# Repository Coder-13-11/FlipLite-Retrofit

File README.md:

# FlipLite Retrofit

A small attachment that flips a bathroom fan switch and turns it off on a timer. The plug-in tube light will use an Amazon smart plug through Alexa.

Start with one fan attachment and one smart plug. The fan arm should park clear so the switch still works by hand. The adjustable fan timer starts at 12 minutes and runs locally. Check that the tube light comes back on when power returns before relying on its smart plug.

## Files

| Folder or file | Contents |
|---|---|
| [CAD](design/cad) | Editable Python parameters, STEP solids and STL print candidates |
| [Electronics](design/electronics) | Editable EAGLE schematic, unrouted board and component list |
| [KiCad board](design/A1/electronics/node.kicad_pcb) | Imported placement draft |
| [Control code](design/firmware) | Python behavior reference and tests |
| [Firmware draft](design/A1/firmware) | Incomplete ESP32 scaffolding |
| [Current plan](design/design-basis.md) | Fan servo plus tube smart plug |
| [Build list](design/active-build-list.md) | Current quantities and print scope |
| [BOM](bom.csv) | Parts categories and links; incomplete pricing |
| [Build guide](design/assembly-and-test.md) | Fit checks and bench tests still needed |
| [Status](STATUS.md) | What exists and what is missing |

## Status

The design is unfinished. The PCB needs routing, verified footprints and electrical checks. The battery is not selected. Firmware and a complete assembly with electronics still need work. No physical prototype has been built or tested.

Inline cradle/finger/optical files are from an earlier approach and are not part of the current build. See [retired files](design/cad/RETIRED.md). Images are CAD or placement renders, not photographs or screenshots of a finished device.

## Checks

Earlier A0 reports recorded 21 passing checks. The upload rerun passed 20; one geometry test could not import OCP.OCP. These tests cover selected geometry/interfaces and control rules, not physical or electrical performance.

```sh
python -m pip install cadquery==2.8.0 trimesh matplotlib pytest
python -m pytest design/validation/test_artifacts.py design/firmware/test_control.py -q
```

## Assistance

AI helped create the CAD, circuit drafts, code and documentation. The files need the builder's own review and revisions. This repository does not establish eligibility for a funding program.

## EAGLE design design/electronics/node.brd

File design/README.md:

# Design files

Start with the [repository README](../README.md) and [current plan](design-basis.md).

The current build uses a servo for the bathroom fan and a smart plug for the tube light. Older inline actuator parts are retained as history and should not be printed for this build.

[Status and missing requirements](../STATUS.md) lists what still needs to be finished. [View notes](previews/README.md) explains the simplified renders.

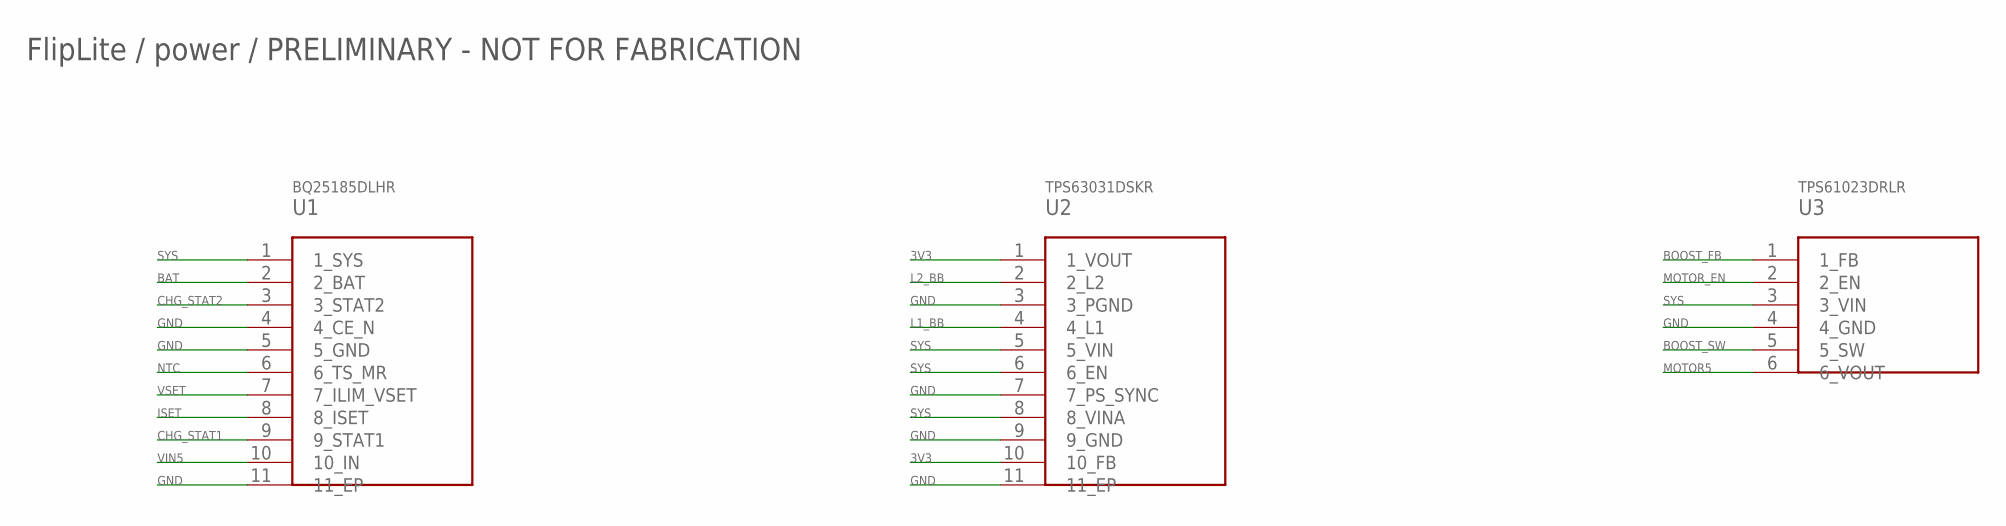
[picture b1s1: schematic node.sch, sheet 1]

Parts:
U1: BQ25185DLHR; U1_PKG
U2: TPS63031DSKR; U2_PKG
U3: TPS61023DRLR; U3_PKG

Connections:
3V3: U2.1 (1_VOUT), U2.10 (10_FB); also elsewhere on the board
BAT: U1.2 (2_BAT); also elsewhere on the board
BOOST_FB: U3.1 (1_FB); also elsewhere on the board
BOOST_SW: U3.5 (5_SW); also elsewhere on the board
CHG_STAT1: U1.9 (9_STAT1); also elsewhere on the board
CHG_STAT2: U1.3 (3_STAT2); also elsewhere on the board
GND: U1.4 (4_CE_N), U1.5 (5_GND), U1.11 (11_EP), U2.3 (3_PGND), U2.7 (7_PS_SYNC), U2.9 (9_GND), U2.11 (11_EP), U3.4 (4_GND); also elsewhere on the board
ISET: U1.8 (8_ISET); also elsewhere on the board
L1_BB: U2.4 (4_L1); also elsewhere on the board
L2_BB: U2.2 (2_L2); also elsewhere on the board
MOTOR5: U3.6 (6_VOUT); also elsewhere on the board
MOTOR_EN: U3.2 (2_EN); also elsewhere on the board
NTC: U1.6 (6_TS_MR); also elsewhere on the board
SYS: U1.1 (1_SYS), U2.5 (5_VIN), U2.6 (6_EN), U2.8 (8_VINA), U3.3 (3_VIN); also elsewhere on the board
VIN5: U1.10 (10_IN); also elsewhere on the board
VSET: U1.7 (7_ILIM_VSET); also elsewhere on the board

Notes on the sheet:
FlipLite / power / PRELIMINARY - NOT FOR FABRICATION

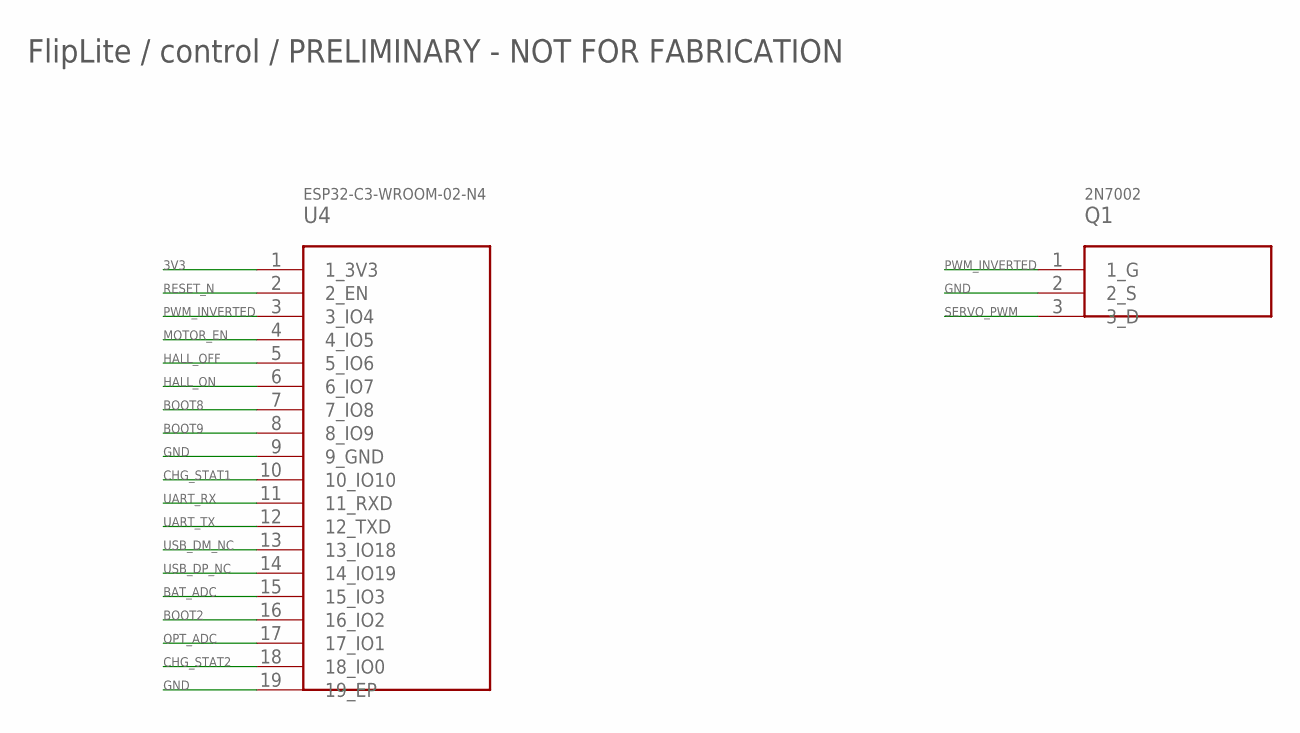
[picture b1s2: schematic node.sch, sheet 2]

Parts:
Q1: 2N7002; Q1_PKG
U4: ESP32-C3-WROOM-02-N4; U4_PKG

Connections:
3V3: U4.1 (1_3V3); also elsewhere on the board
BAT_ADC: U4.15 (15_IO3); also elsewhere on the board
BOOT2: U4.16 (16_IO2); also elsewhere on the board
BOOT8: U4.7 (7_IO8); also elsewhere on the board
BOOT9: U4.8 (8_IO9); also elsewhere on the board
CHG_STAT1: U4.10 (10_IO10); also elsewhere on the board
CHG_STAT2: U4.18 (18_IO0); also elsewhere on the board
GND: Q1.2 (2_S), U4.9 (9_GND), U4.19 (19_EP); also elsewhere on the board
HALL_OFF: U4.5 (5_IO6); also elsewhere on the board
HALL_ON: U4.6 (6_IO7); also elsewhere on the board
MOTOR_EN: U4.4 (4_IO5); also elsewhere on the board
OPT_ADC: U4.17 (17_IO1); also elsewhere on the board
PWM_INVERTED: Q1.1 (1_G), U4.3 (3_IO4); also elsewhere on the board
RESET_N: U4.2 (2_EN); also elsewhere on the board
SERVO_PWM: Q1.3 (3_D); also elsewhere on the board
UART_RX: U4.11 (11_RXD); also elsewhere on the board
UART_TX: U4.12 (12_TXD); also elsewhere on the board
USB_DM_NC: U4.13 (13_IO18)
USB_DP_NC: U4.14 (14_IO19)

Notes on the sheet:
FlipLite / control / PRELIMINARY - NOT FOR FABRICATION

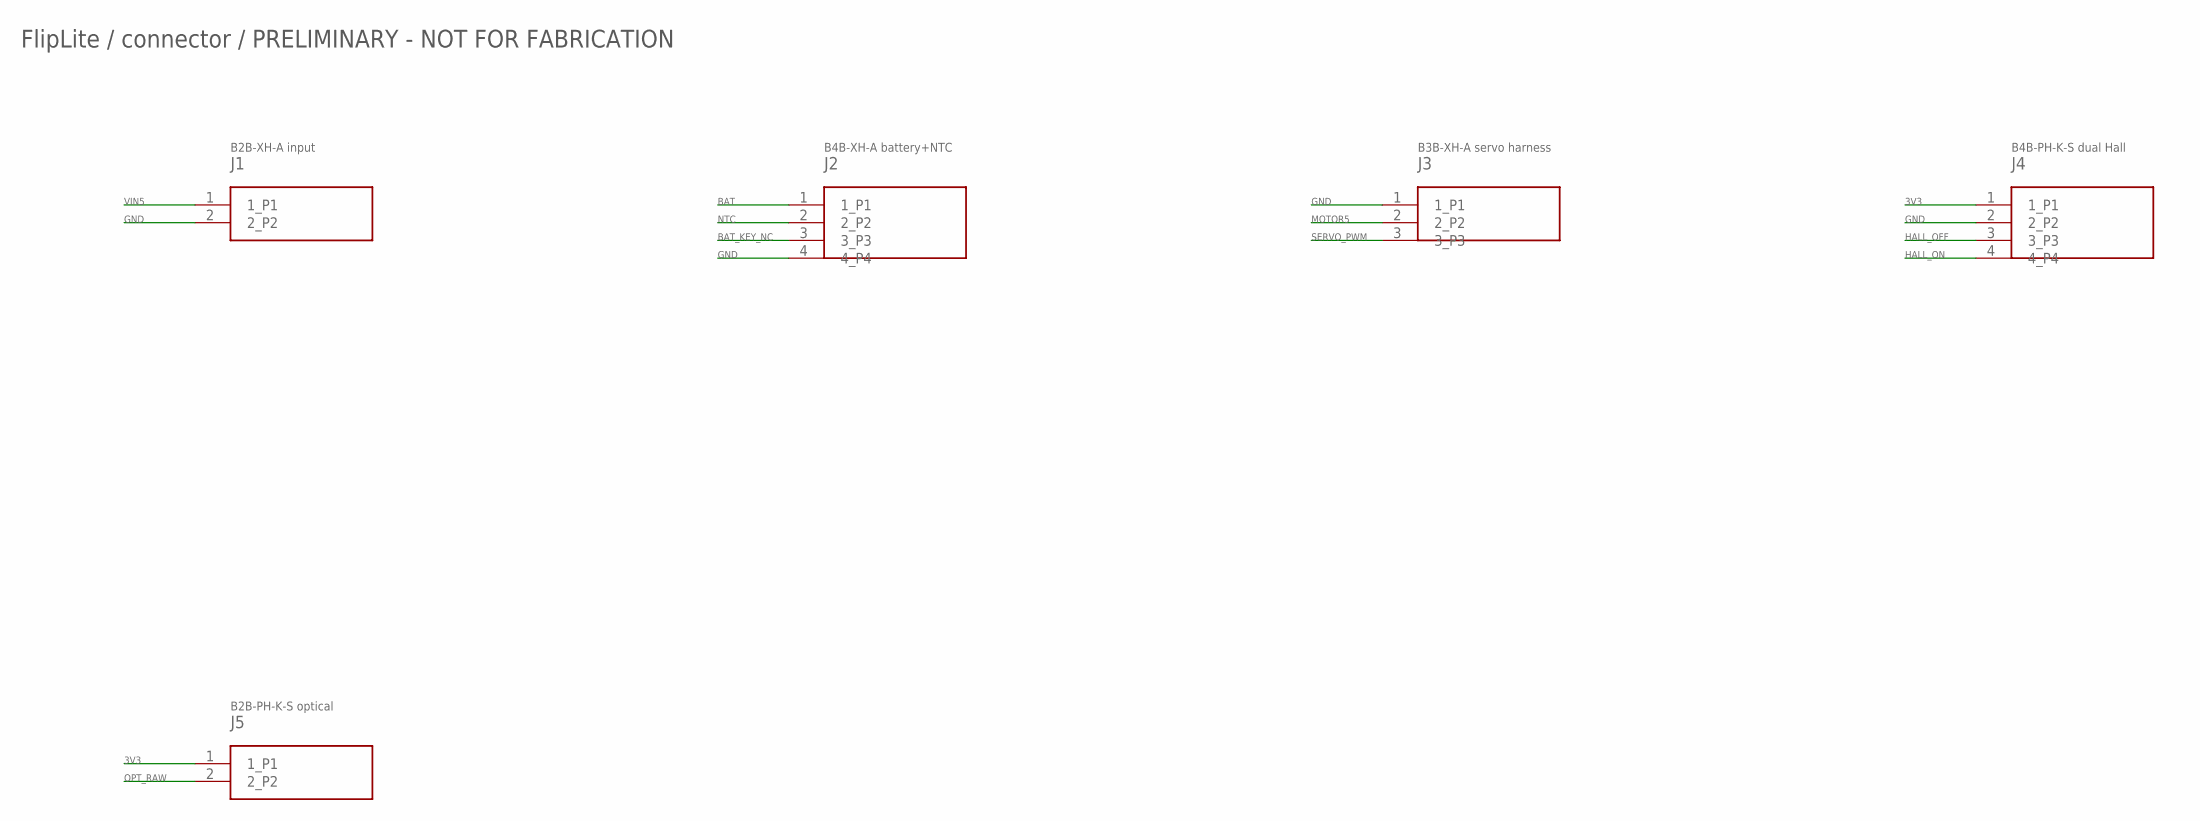
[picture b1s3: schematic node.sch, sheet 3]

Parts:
J1: B2B-XH-A input; J1_PKG
J2: B4B-XH-A battery+NTC; J2_PKG
J3: B3B-XH-A servo harness; J3_PKG
J4: B4B-PH-K-S dual Hall; J4_PKG
J5: B2B-PH-K-S optical; J5_PKG

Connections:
3V3: J4.1 (1_P1), J5.1 (1_P1); also elsewhere on the board
BAT: J2.1 (1_P1); also elsewhere on the board
BAT_KEY_NC: J2.3 (3_P3)
GND: J1.2 (2_P2), J2.4 (4_P4), J3.1 (1_P1), J4.2 (2_P2); also elsewhere on the board
HALL_OFF: J4.3 (3_P3); also elsewhere on the board
HALL_ON: J4.4 (4_P4); also elsewhere on the board
MOTOR5: J3.2 (2_P2); also elsewhere on the board
NTC: J2.2 (2_P2); also elsewhere on the board
OPT_RAW: J5.2 (2_P2); also elsewhere on the board
SERVO_PWM: J3.3 (3_P3); also elsewhere on the board
VIN5: J1.1 (1_P1); also elsewhere on the board

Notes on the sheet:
FlipLite / connector / PRELIMINARY - NOT FOR FABRICATION

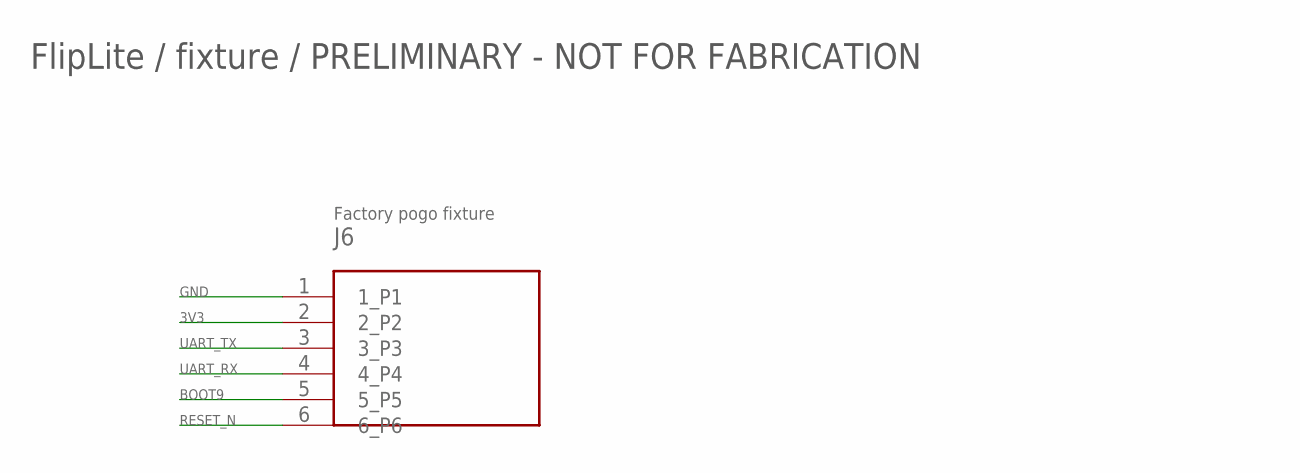
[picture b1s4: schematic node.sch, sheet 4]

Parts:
J6: Factory pogo fixture; J6_PKG

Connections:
3V3: J6.2 (2_P2); also elsewhere on the board
BOOT9: J6.5 (5_P5); also elsewhere on the board
GND: J6.1 (1_P1); also elsewhere on the board
RESET_N: J6.6 (6_P6); also elsewhere on the board
UART_RX: J6.4 (4_P4); also elsewhere on the board
UART_TX: J6.3 (3_P3); also elsewhere on the board

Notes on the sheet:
FlipLite / fixture / PRELIMINARY - NOT FOR FABRICATION

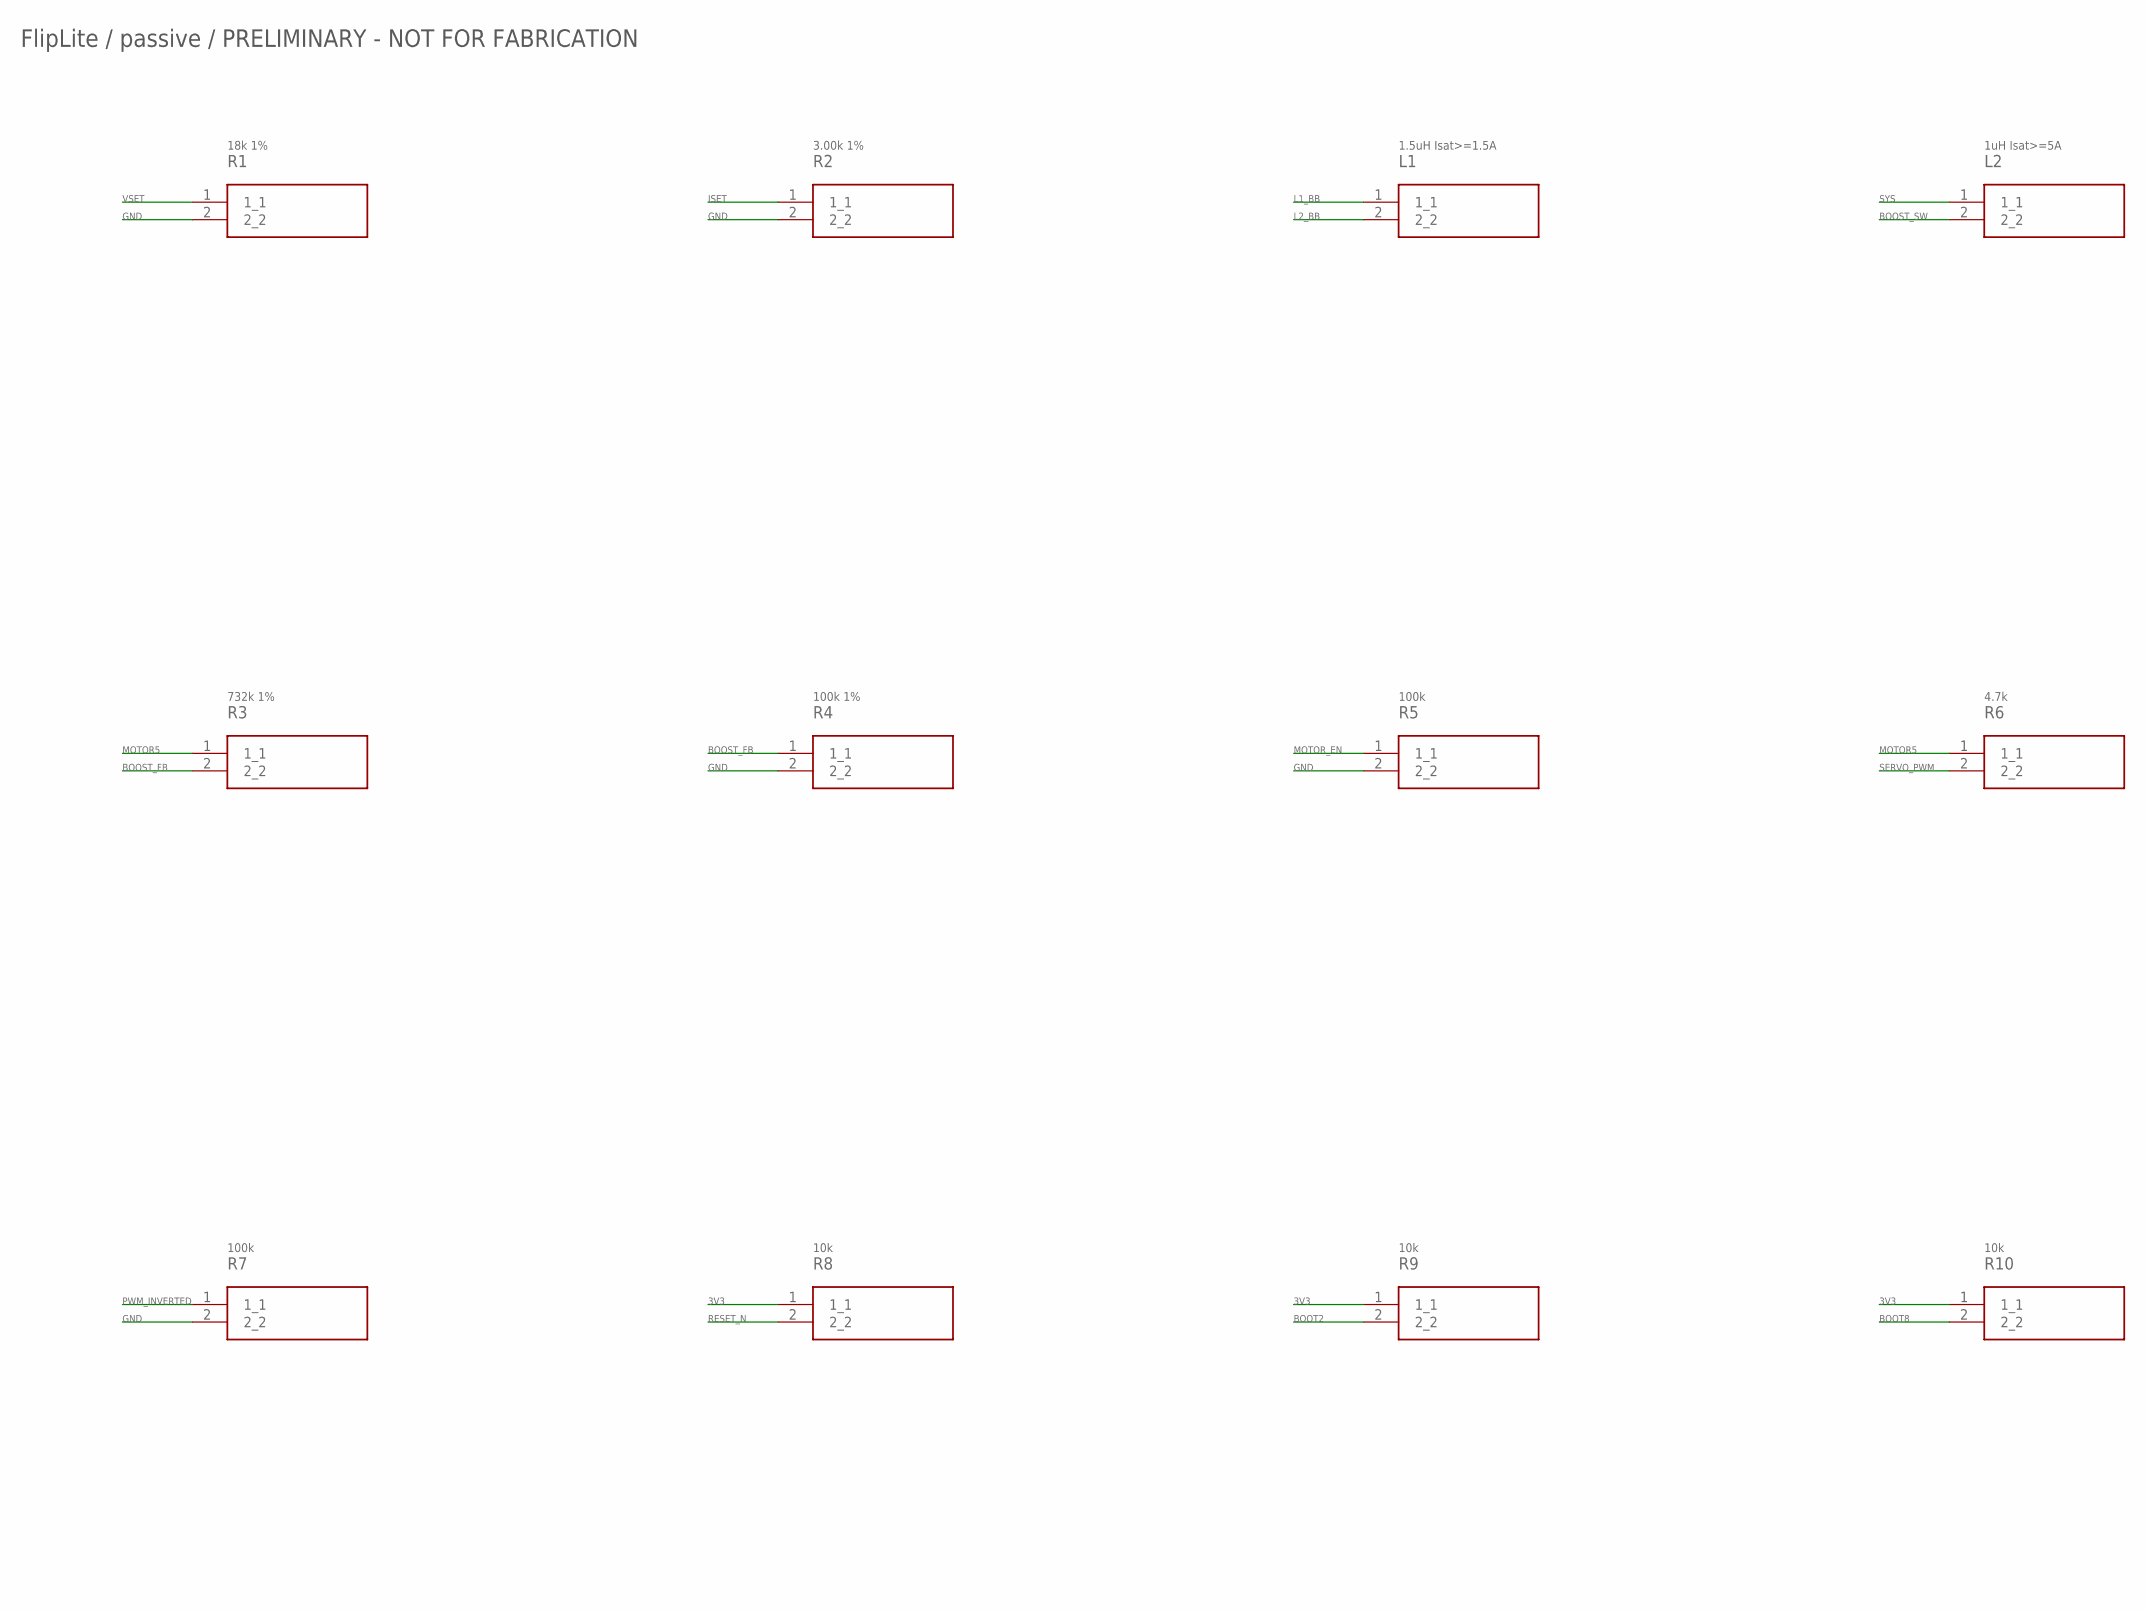
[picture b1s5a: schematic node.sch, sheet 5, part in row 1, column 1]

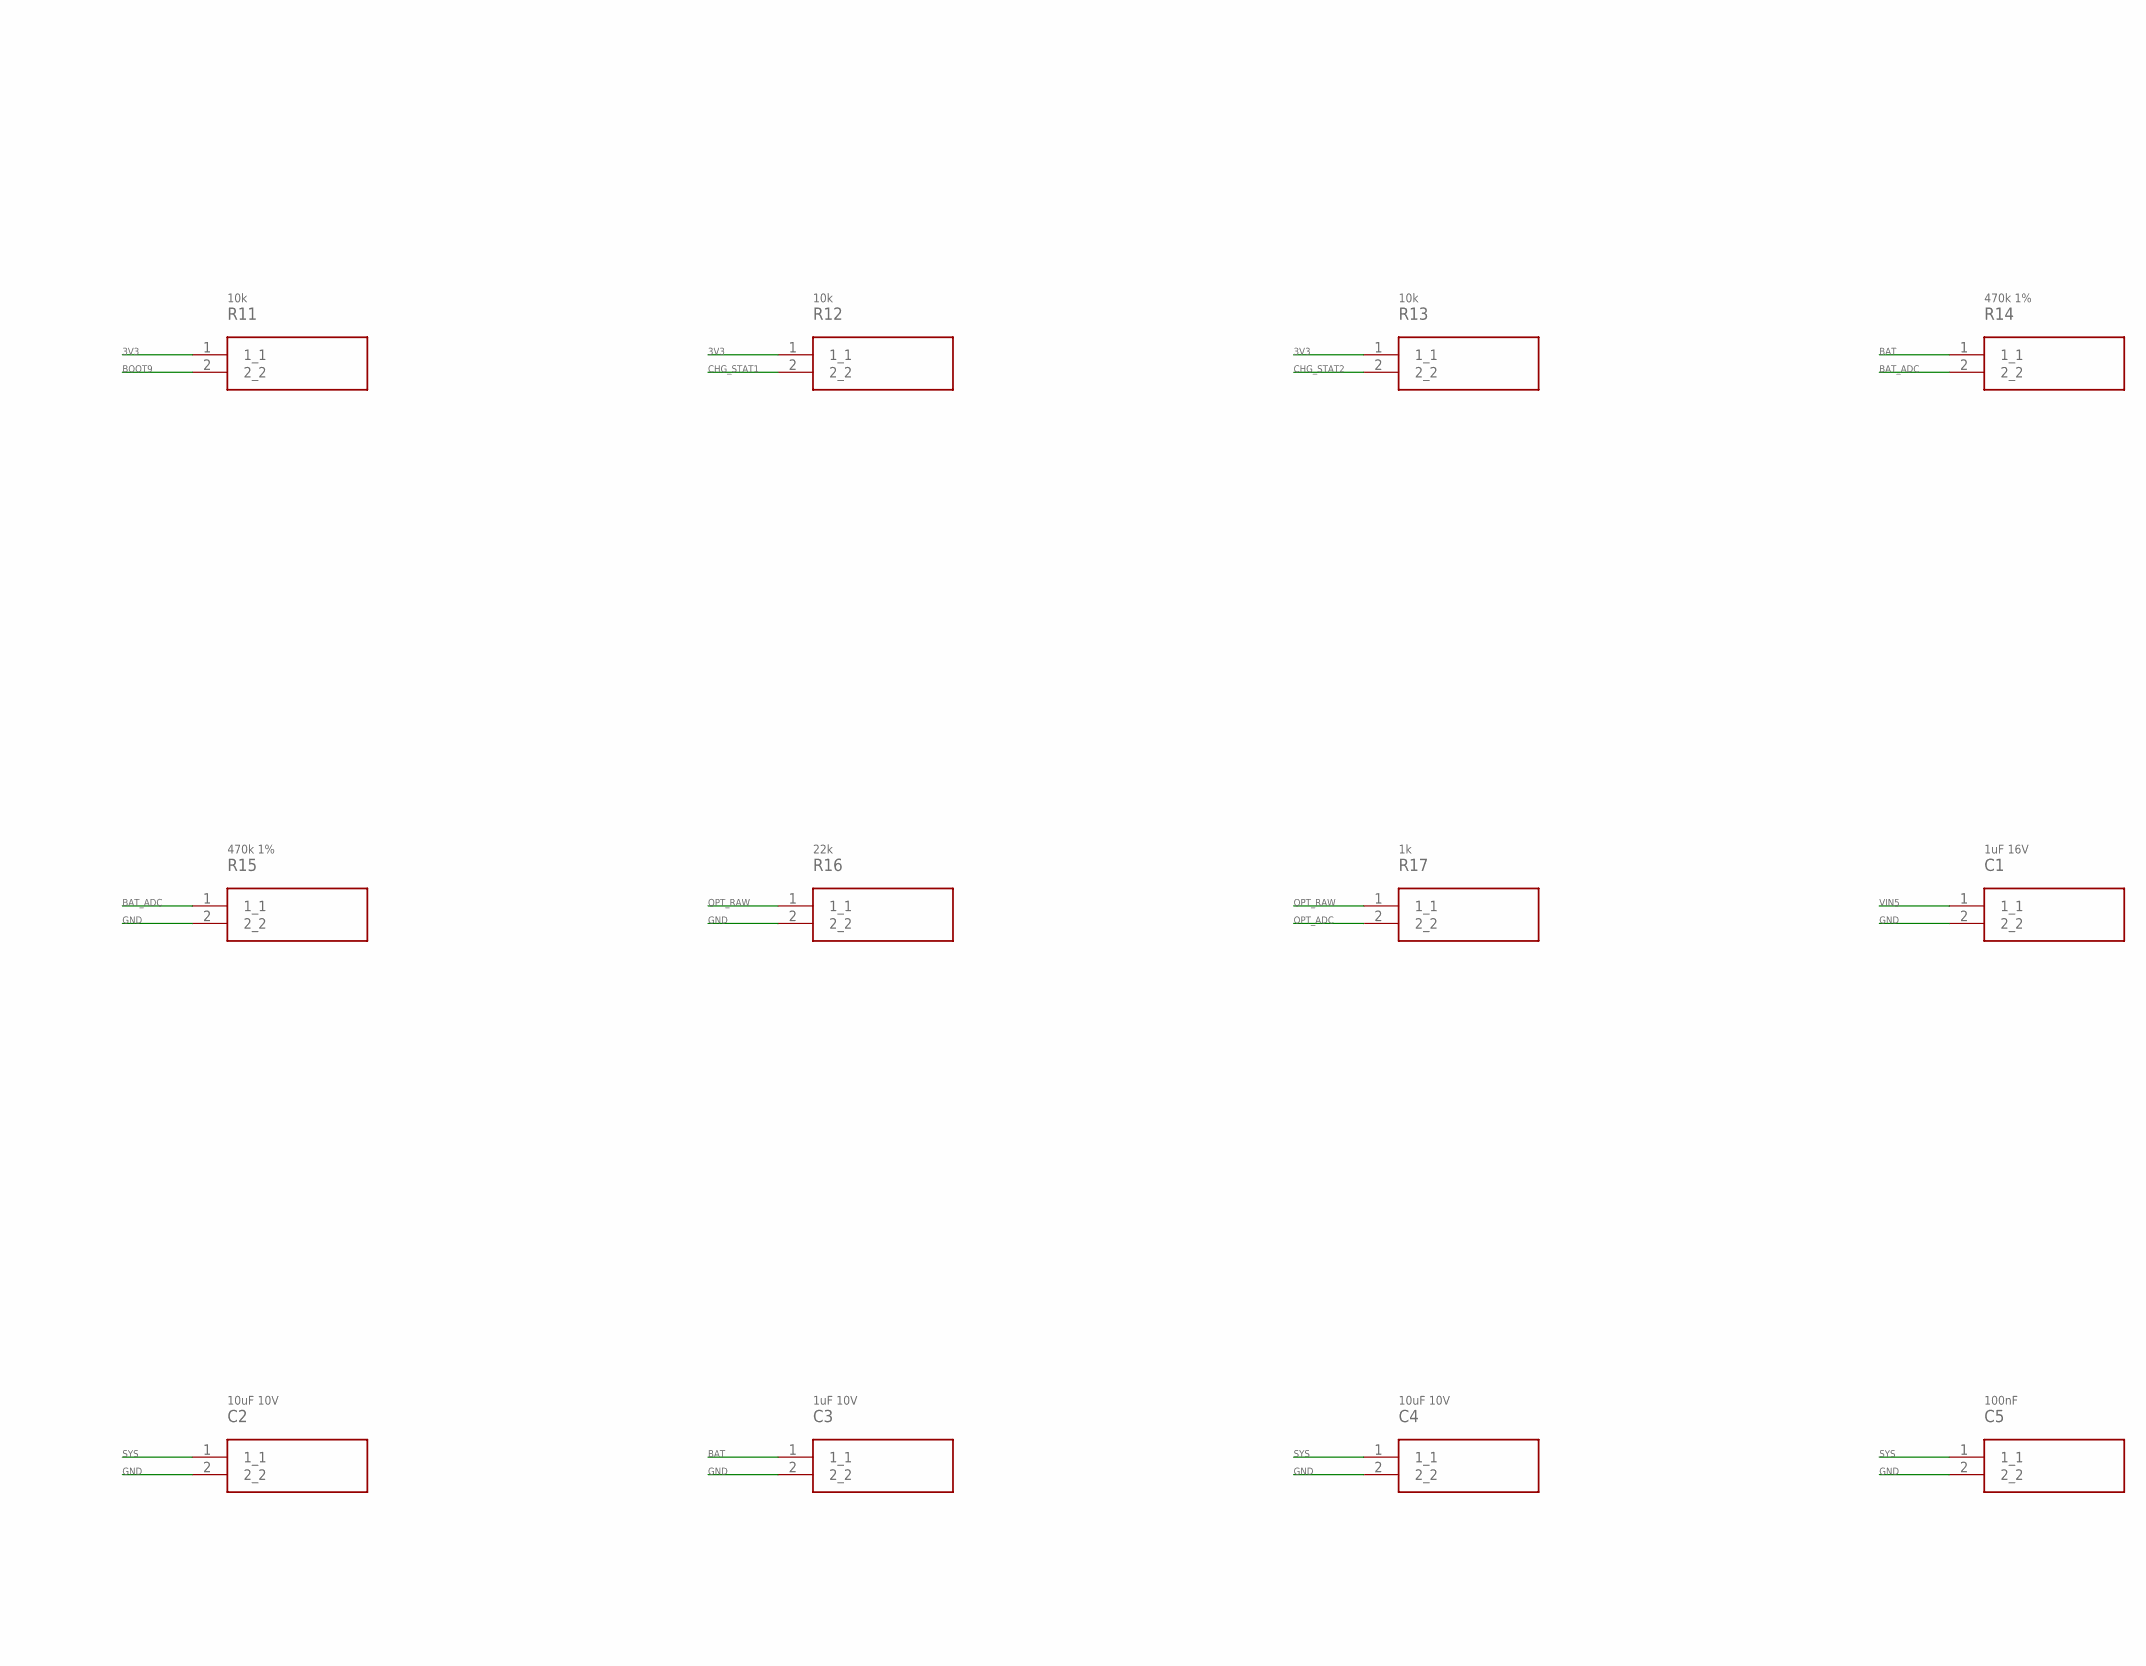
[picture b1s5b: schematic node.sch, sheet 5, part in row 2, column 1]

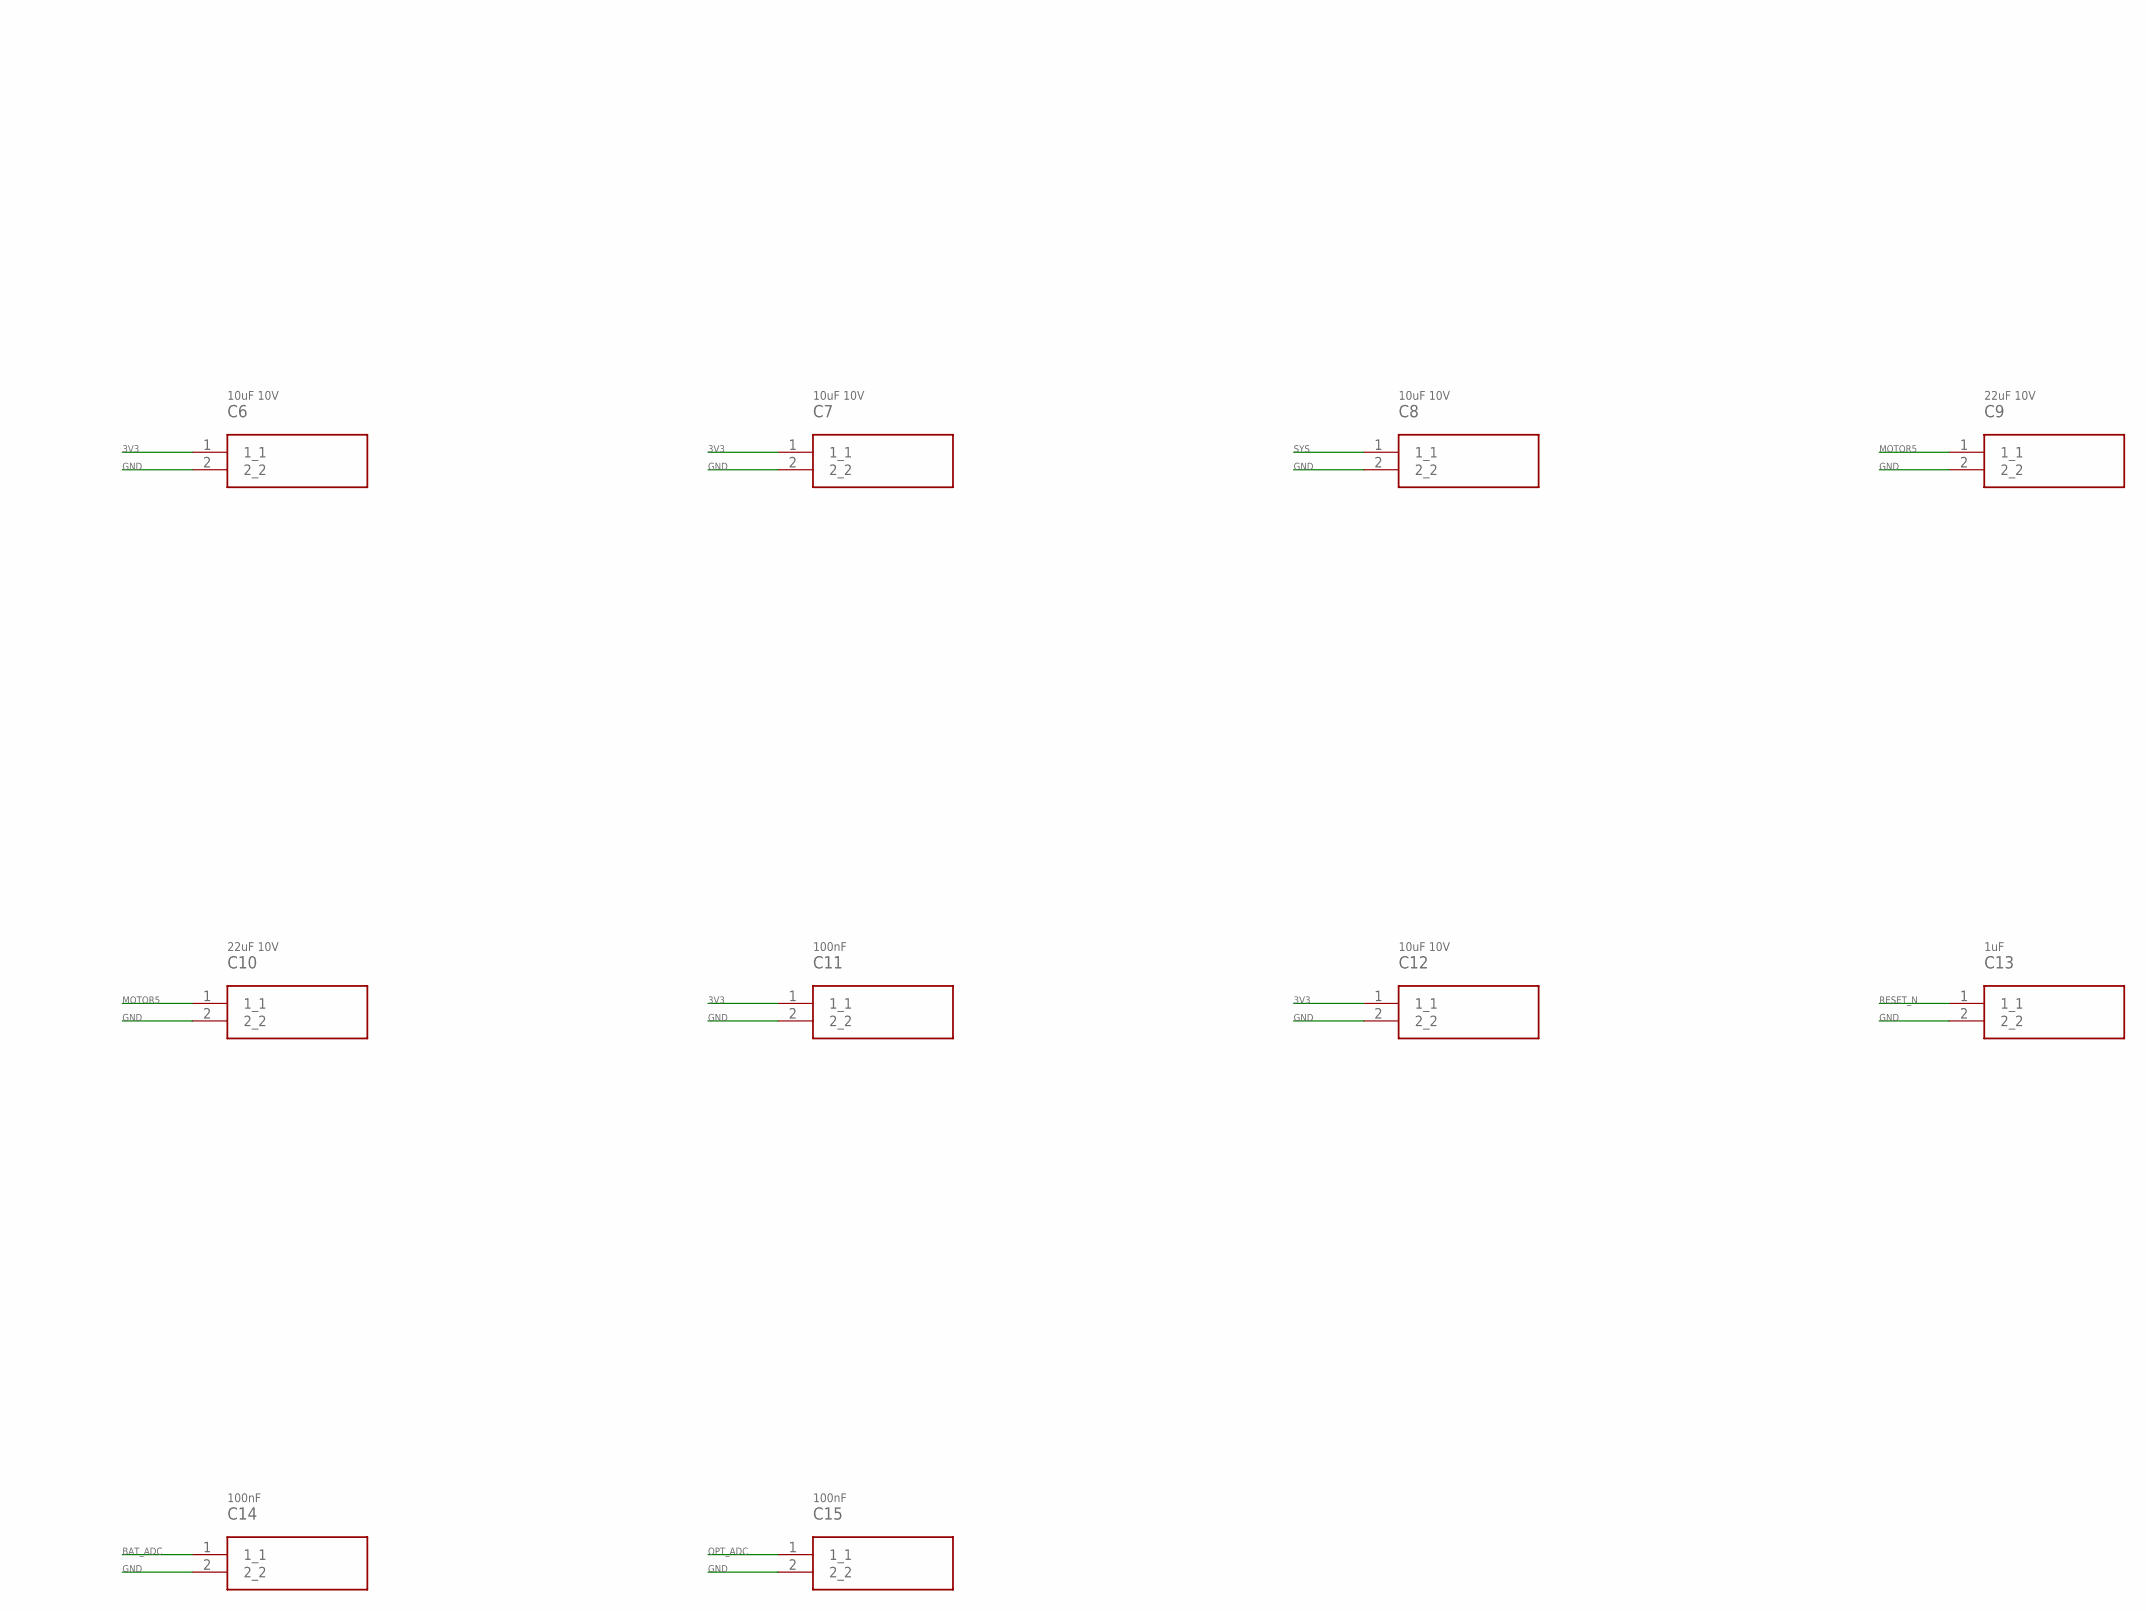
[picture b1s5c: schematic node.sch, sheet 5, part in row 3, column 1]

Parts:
C1: 1uF 16V; C1_PKG
C2: 10uF 10V; C2_PKG
C3: 1uF 10V; C3_PKG
C4: 10uF 10V; C4_PKG
C5: 100nF; C5_PKG
C6: 10uF 10V; C6_PKG
C7: 10uF 10V; C7_PKG
C8: 10uF 10V; C8_PKG
C9: 22uF 10V; C9_PKG
C10: 22uF 10V; C10_PKG
C11: 100nF; C11_PKG
C12: 10uF 10V; C12_PKG
C13: 1uF; C13_PKG
C14: 100nF; C14_PKG
C15: 100nF; C15_PKG
L1: 1.5uH Isat>=1.5A; L1_PKG
L2: 1uH Isat>=5A; L2_PKG
R1: 18k 1%; R1_PKG
R2: 3.00k 1%; R2_PKG
R3: 732k 1%; R3_PKG
R4: 100k 1%; R4_PKG
R5: 100k; R5_PKG
R6: 4.7k; R6_PKG
R7: 100k; R7_PKG
R8: 10k; R8_PKG
R9: 10k; R9_PKG
R10: 10k; R10_PKG
R11: 10k; R11_PKG
R12: 10k; R12_PKG
R13: 10k; R13_PKG
R14: 470k 1%; R14_PKG
R15: 470k 1%; R15_PKG
R16: 22k; R16_PKG
R17: 1k; R17_PKG

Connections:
3V3: C6.1 (1_1), C7.1 (1_1), C11.1 (1_1), C12.1 (1_1), R8.1 (1_1), R9.1 (1_1), R10.1 (1_1), R11.1 (1_1), R12.1 (1_1), R13.1 (1_1); also elsewhere on the board
BAT: C3.1 (1_1), R14.1 (1_1); also elsewhere on the board
BAT_ADC: C14.1 (1_1), R14.2 (2_2), R15.1 (1_1); also elsewhere on the board
BOOST_FB: R3.2 (2_2), R4.1 (1_1); also elsewhere on the board
BOOST_SW: L2.2 (2_2); also elsewhere on the board
BOOT2: R9.2 (2_2); also elsewhere on the board
BOOT8: R10.2 (2_2); also elsewhere on the board
BOOT9: R11.2 (2_2); also elsewhere on the board
CHG_STAT1: R12.2 (2_2); also elsewhere on the board
CHG_STAT2: R13.2 (2_2); also elsewhere on the board
GND: C1.2 (2_2), C2.2 (2_2), C3.2 (2_2), C4.2 (2_2), C5.2 (2_2), C6.2 (2_2), C7.2 (2_2), C8.2 (2_2), C9.2 (2_2), C10.2 (2_2), C11.2 (2_2), C12.2 (2_2), C13.2 (2_2), C14.2 (2_2), C15.2 (2_2), R1.2 (2_2), R2.2 (2_2), R4.2 (2_2), R5.2 (2_2), R7.2 (2_2), R15.2 (2_2), R16.2 (2_2); also elsewhere on the board
ISET: R2.1 (1_1); also elsewhere on the board
L1_BB: L1.1 (1_1); also elsewhere on the board
L2_BB: L1.2 (2_2); also elsewhere on the board
MOTOR5: C9.1 (1_1), C10.1 (1_1), R3.1 (1_1), R6.1 (1_1); also elsewhere on the board
MOTOR_EN: R5.1 (1_1); also elsewhere on the board
OPT_ADC: C15.1 (1_1), R17.2 (2_2); also elsewhere on the board
OPT_RAW: R16.1 (1_1), R17.1 (1_1); also elsewhere on the board
PWM_INVERTED: R7.1 (1_1); also elsewhere on the board
RESET_N: C13.1 (1_1), R8.2 (2_2); also elsewhere on the board
SERVO_PWM: R6.2 (2_2); also elsewhere on the board
SYS: C2.1 (1_1), C4.1 (1_1), C5.1 (1_1), C8.1 (1_1), L2.1 (1_1); also elsewhere on the board
VIN5: C1.1 (1_1); also elsewhere on the board
VSET: R1.1 (1_1); also elsewhere on the board

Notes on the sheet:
FlipLite / passive / PRELIMINARY - NOT FOR FABRICATION

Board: 1 copper layer, 45 parts (0 on the bottom side), 29 nets, no tracks yet.

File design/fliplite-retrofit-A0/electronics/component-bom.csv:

Reference,Value_or_candidate,Quantity_per_node,Source,Release_status
U1,BQ25185DLHR,1,https://www.ti.com/lit/ds/symlink/bq25185.pdf,engineering candidate; footprint/MPN/availability not released
U2,TPS63031DSKR,1,https://www.ti.com/lit/ds/symlink/tps63031.pdf,engineering candidate; footprint/MPN/availability not released
U3,TPS61023DRLR,1,https://www.ti.com/lit/ds/symlink/tps61023.pdf,engineering candidate; footprint/MPN/availability not released
U4,ESP32-C3-WROOM-02-N4,1,https://www.espressif.com/sites/default/files/documentation/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,engineering candidate; footprint/MPN/availability not released
Q1,2N7002,1,https://www.nexperia.com/product/2N7002,engineering candidate; footprint/MPN/availability not released
J1,B2B-XH-A input,1,https://www.jst-mfg.com/product/index.php?series=277,engineering candidate; footprint/MPN/availability not released
J2,B4B-XH-A battery+NTC,1,https://www.jst-mfg.com/product/index.php?series=277,engineering candidate; footprint/MPN/availability not released
J3,B3B-XH-A servo harness,1,https://www.jst-mfg.com/product/index.php?series=277,engineering candidate; footprint/MPN/availability not released
J4,B4B-PH-K-S dual Hall,1,https://www.jst-mfg.com/product/index.php?series=199,engineering candidate; footprint/MPN/availability not released
J5,B2B-PH-K-S optical,1,https://www.jst-mfg.com/product/index.php?series=199,engineering candidate; footprint/MPN/availability not released
J6,Factory pogo fixture,1,https://www.jst-mfg.com/product/index.php?series=199,engineering candidate; footprint/MPN/availability not released
R1,18k 1%,1,https://www.yageo.com/en/Product,engineering candidate; footprint/MPN/availability not released
R2,3.00k 1%,1,https://www.yageo.com/en/Product,engineering candidate; footprint/MPN/availability not released
L1,1.5uH Isat>=1.5A,1,https://www.coilcraft.com/en-us/products/power/shielded-indu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,engineering candidate; footprint/MPN/availability not released
L2,1uH Isat>=5A,1,https://www.coilcraft.com/en-us/products/power/shielded-indu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,engineering candidate; footprint/MPN/availability not released
R3,732k 1%,1,https://www.yageo.com/en/Product,engineering candidate; footprint/MPN/availability not released
R4,100k 1%,1,https://www.yageo.com/en/Product,engineering candidate; footprint/MPN/availability not released
R5,100k,1,https://www.yageo.com/en/Product,engineering candidate; footprint/MPN/availability not released
R6,4.7k,1,https://www.yageo.com/en/Product,engineering candidate; footprint/MPN/availability not released
R7,100k,1,https://www.yageo.com/en/Product,engineering candidate; footprint/MPN/availability not released
R8,10k,1,https://www.yageo.com/en/Product,engineering candidate; footprint/MPN/availability not released
R9,10k,1,https://www.yageo.com/en/Product,engineering candidate; footprint/MPN/availability not released
R10,10k,1,https://www.yageo.com/en/Product,engineering candidate; footprint/MPN/availability not released
R11,10k,1,https://www.yageo.com/en/Product,engineering candidate; footprint/MPN/availability not released
R12,10k,1,https://www.yageo.com/en/Product,engineering candidate; footprint/MPN/availability not released
R13,10k,1,https://www.yageo.com/en/Product,engineering candidate; footprint/MPN/availability not released
R14,470k 1%,1,https://www.yageo.com/en/Product,engineering candidate; footprint/MPN/availability not released
R15,470k 1%,1,https://www.yageo.com/en/Product,engineering candidate; footprint/MPN/availability not released
R16,22k,1,https://www.yageo.com/en/Product,engineering candidate; footprint/MPN/availability not released
R17,1k,1,https://www.yageo.com/en/Product,engineering candidate; footprint/MPN/availability not released
C1,1uF 16V,1,https://www.yageo.com/en/Product,engineering candidate; footprint/MPN/availability not released
C2,10uF 10V,1,https://www.yageo.com/en/Product,engineering candidate; footprint/MPN/availability not released
C3,1uF 10V,1,https://www.yageo.com/en/Product,engineering candidate; footprint/MPN/availability not released
C4,10uF 10V,1,https://www.yageo.com/en/Product,engineering candidate; footprint/MPN/availability not released
C5,100nF,1,https://www.yageo.com/en/Product,engineering candidate; footprint/MPN/availability not released
C6,10uF 10V,1,https://www.yageo.com/en/Product,engineering candidate; footprint/MPN/availability not released
C7,10uF 10V,1,https://www.yageo.com/en/Product,engineering candidate; footprint/MPN/availability not released
C8,10uF 10V,1,https://www.yageo.com/en/Product,engineering candidate; footprint/MPN/availability not released
C9,22uF 10V,1,https://www.yageo.com/en/Product,engineering candidate; footprint/MPN/availability not released
C10,22uF 10V,1,https://www.yageo.com/en/Product,engineering candidate; footprint/MPN/availability not released
C11,100nF,1,https://www.yageo.com/en/Product,engineering candidate; footprint/MPN/availability not released
C12,10uF 10V,1,https://www.yageo.com/en/Product,engineering candidate; footprint/MPN/availability not released
C13,1uF,1,https://www.yageo.com/en/Product,engineering candidate; footprint/MPN/availability not released
C14,100nF,1,https://www.yageo.com/en/Product,engineering candidate; footprint/MPN/availability not released
C15,100nF,1,https://www.yageo.com/en/Product,engineering candidate; footprint/MPN/availability not released
